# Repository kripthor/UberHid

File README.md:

# UberHid

Wifi keylogger with keyboard and mouse injection capabilities.

```bash
├── docs # docs and pictures
├── firmware # firmware code
│ ├── UberHID-ESPUSB # ESP8266 firmware
│ │ └── data # ESP8266 static files
│ └── UberHID-Leonardo # ATmega32u4 firmware
└── hardware # hardware schematics
```

## Bill of Materials

| Qty. | Description | Obs. |
|------|------------------------|-----------------------------------------------------------------|
| 1 | UBERHid PCB | Designed by [@kripthor](https://github.com/kripthor/UberHid/) |
| 1 | Arduino atmega32u4 | Board is designed for DM Micro AU version (Beetle with 18 pins) |
| 1 | ESP8266 ESP-12E module | Module to solder |
| 1 | MAX3421EEHJ+ USB | USB Peripheral Host Controller 32-Pin |
| 5 | 10kΩ Resistor | SMD. |
| 2 | 33Ω Resistor | SMD. |
| 2 | 18pF Capacitator | SMD. |
| 1 | XTAL TXC 12Mhz | SMD. |
| 1 | 2k2 Resistor | 2.2KΩ SMD. |
| 1 | FTDI FT232RL | USB to TTL Serial 3.3V/5V USB Adapter or equivalent. Used to program the ESP8266. |

* All the components can be found in the usual online stores such as *Aliexpress* and *eBay*.

## Schematics

### UBERHid PCB

### UBERHid Schematic

### UBERHid Wiring 

Details of the wiring between the ATmega32u4 and FTDI programmer. Note that the ATmega used in this case was an SS Micro version which does not have the same pinout as the recommended DM Micro AU Beetle Leonardo, which fits directly in the PCB pinout layout.

## Soldering

The components must be soldered accordingly to the above schematic. Some extra details and _protips_:

- Start by sodering the smaller components, especially the MAX3421 chip, the SMD resistors and capacitors and the XTAL crystal.
- Two pins stay right bellow the ESP8266 chip. You have to be sure that these pins do not make any contact with the ESP8266 after the soldering is completed. I used a little of heat-resistant isolator tape to avoid any contact and soldered the pins on the other side of the board.
- Solder the ESP8266 before the remaining pinouts to have more space. 
- Finish the soldering by adding the remaining pins and the USB port.
- The atmega32u4 can be soldered directly on top of the UBERHid PCB, although some jumper cables can also be used to make it possible to reuse it to other projects.
- Clean the board using isopropyl alcohol.

## How to program the devices

### Using [Platformio](https://platformio.org/)

#### ESP8266

0. Connect the FTDI to the PCB pins as depicted in the wiring scheme above.
1. GPIO0 is needs to be grounded to get into programming mode.
2. Uncomment the follwing lines in ```platformio.ini```:
```yaml
src_dir = ${workspacedir}/firmware/UberHID-ESPUSB/.
data_dir = ${workspacedir}/firmware/UberHID-ESPUSB/data/.
```
3. ```$ platformio run -e esp12e``` _sanity check_
4. ```$ platformio run -e esp12e --target upload --upload-port <dev/ttyUSB*>``` _uploads firmware_
 - Replace ```<dev/ttyUSB*>``` with your device, _e.g._: ```dev/ttyUSB0```
5. ```$ pio run -e esp12e --target uploadfs --upload-port <dev/ttyUSB*>``` _uploads filesystem (data folder)_
 - Replace ```<dev/ttyUSB*>``` with your device, _e.g._: ```dev/ttyUSB0```

#### Arduino Leonardo (atmega32u4)

0. Plug-in the Arduino Leonardo in one of the computer USB ports.
1. Uncomment the follwing line in ```platformio.ini```:
```yaml
src_dir = ${workspacedir}/firmware/UberHID-Leonardo/.
```
2. ```$ platformio run -e leonardo``` _sanity check_
3. ```$ platformio run -e leonardo --target upload --upload-port <dev/ttyACM*>```
 - Replace ```<dev/ttyACM*>``` with your device, _e.g._: ```dev/ttyACM0```

## How to use it?

0. Connect the device between a keyboard and a computer. 
 ```
 ----------     ---------     ----------
 |Keyboard| <-> |UBERHid| <-> |Computer|
 ----------     ---------     ----------
 ```
1. Connect to the device access point.
 - It can be visible or hidden depending on the configuration on file ```Config.h``` in ```firmware/UberHID-ESPUSB```. Other configurations available are the access point name and password.

 ```C
 #define WIFISSID "UBERHID"
 #define WIFIPASS "uberidiota"
 #define WIFICHANNEL 7
 #define WIFISSIDHIDDEN 0 // 0 for not hidden
 ``` 
2. Navigate to ```192.168.4.1```

3. You can see the keystrokes in realtime and inject keyboard and mouse commands. Also, you can RickRoll your friends.

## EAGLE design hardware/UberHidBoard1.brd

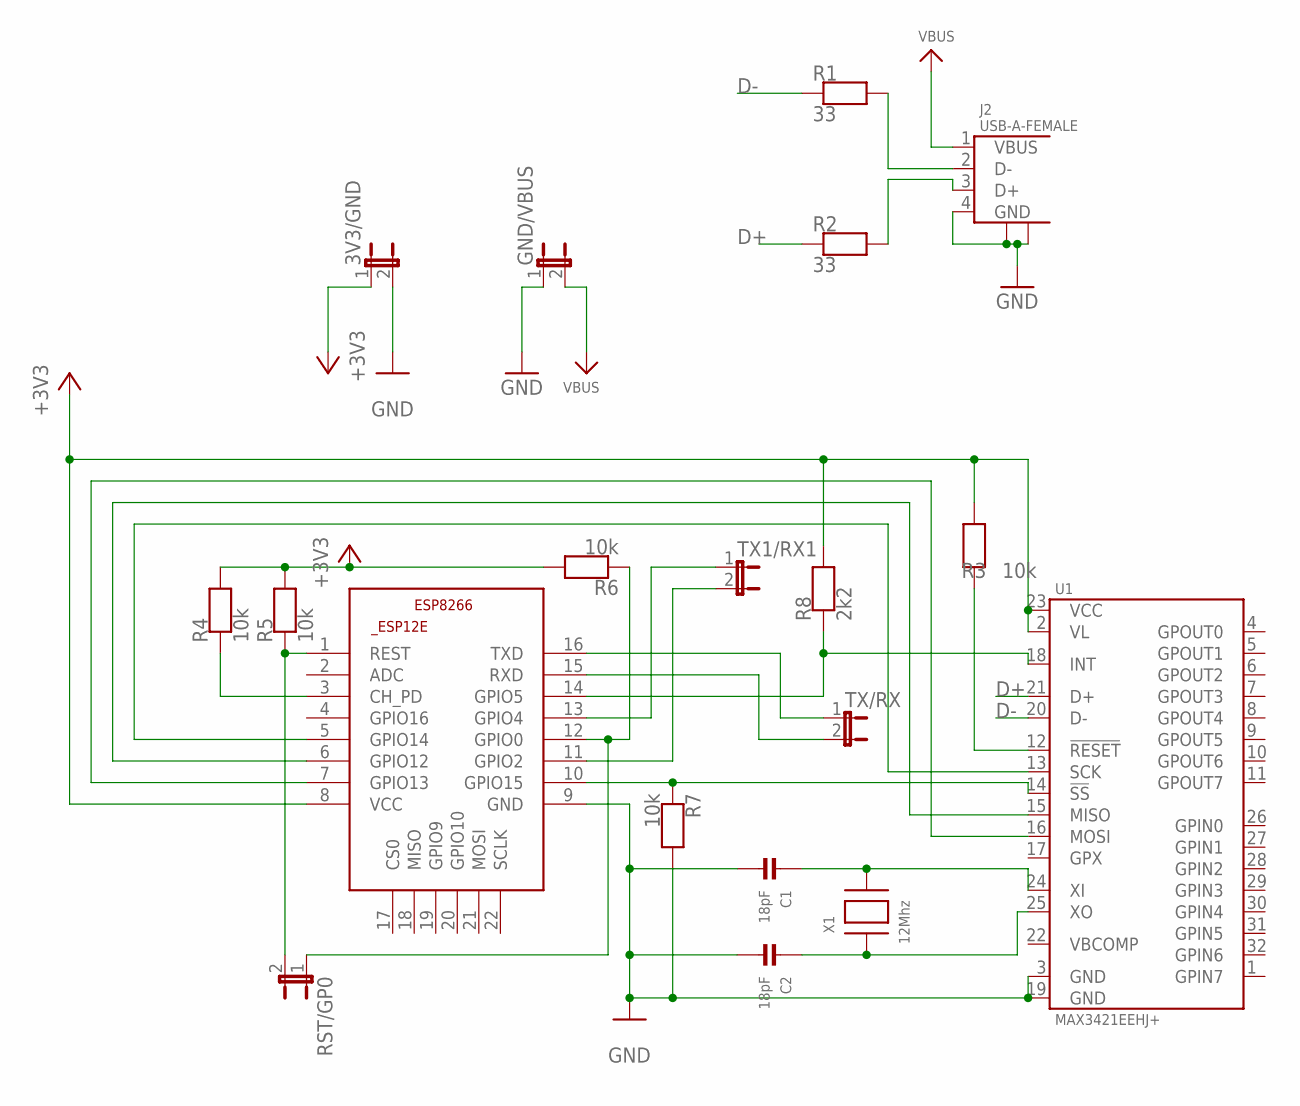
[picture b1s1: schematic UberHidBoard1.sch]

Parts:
3V3/GND: JUMPER2
C1, C2: 18pF; 0805
ESP8266: ESP8266-12EESP12E; ESP8266-ESP12E
GND/VBUS: JUMPER2
J2: USB-A-FEMALE
R1, R2: 33; 0805
R3, R4, R5, R6, R7: 10k; 0805
R8: 2k2; 0805
RST/GP0: JUMPER2
TX1/RX1: JUMPER2
TX/RX: JUMPER2
U1: MAX3421EEHJ+; LQFP-23
X1: 12Mhz; XTAL3215

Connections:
+3V3: 3V3/GND.1, ESP8266.8 (VCC), R3.2, R4.2, R5.2, R6.2, R8.2, U1.2 (VL), U1.23 (VCC)
D+: R2.1, U1.21 (D+)
D-: R1.1, U1.20 (D-)
GND: 3V3/GND.2, C1.2, C2.2, ESP8266.9 (GND), GND/VBUS.1, J2.4 (GND), J2.P$1, J2.P$2, R7.2, U1.3 (GND), U1.19 (GND)
unnamed: J2.2 (D-), R1.2
unnamed: J2.3 (D+), R2.2
unnamed: ESP8266.10 (GPIO15), R7.1, U1.14 (!SS)
unnamed: ESP8266.7 (GPIO13), U1.16 (MOSI)
unnamed: ESP8266.6 (GPIO12), U1.15 (MISO)
unnamed: ESP8266.5 (GPIO14), U1.13 (SCK)
unnamed: R3.1, U1.12 (!RESET)
unnamed: ESP8266.14 (GPIO5), R8.1, U1.18 (INT)
unnamed: C2.1, U1.25 (XO), X1.P$1
unnamed: C1.1, U1.24 (XI), X1.P$2
unnamed: ESP8266.13 (GPIO4), TX1/RX1.1
unnamed: ESP8266.3 (CH_PD), R4.1
unnamed: ESP8266.1 (REST), R5.1, RST/GP0.2
unnamed: ESP8266.12 (GPIO0), R6.1, RST/GP0.1
unnamed: ESP8266.16 (TXD), TX/RX.1
unnamed: ESP8266.15 (RXD), TX/RX.2
unnamed: ESP8266.11 (GPIO2), TX1/RX1.2
VBUS: GND/VBUS.2, J2.1 (VBUS)

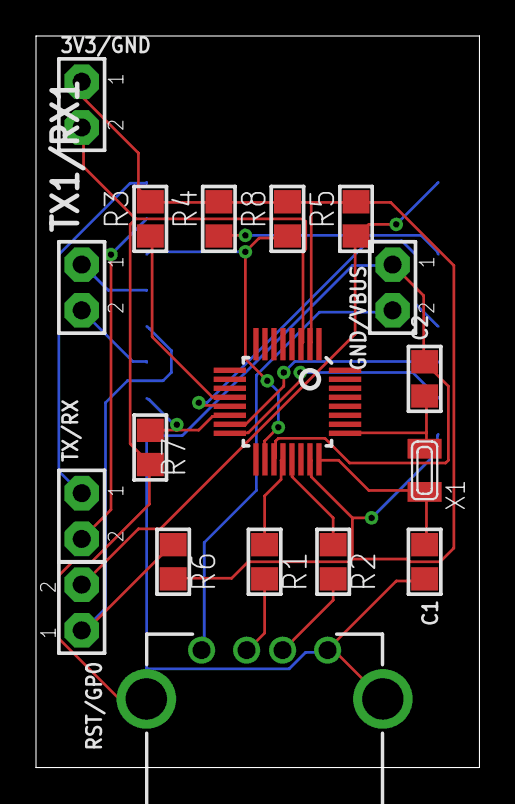
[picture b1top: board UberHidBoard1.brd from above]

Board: 2 copper layers, 24.6 x 40.6 mm, 19 parts (1 on the bottom side), 22 nets.

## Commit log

2019-12-24 add docs. add platformio and gitignore.
2019-12-26 add documentation.
2019-12-26 fix diagram

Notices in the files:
parts and their libraries:
microbuilder: This work is placed in the public domain, and may be freely used for commercial and non-commercial work with the following conditions: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
